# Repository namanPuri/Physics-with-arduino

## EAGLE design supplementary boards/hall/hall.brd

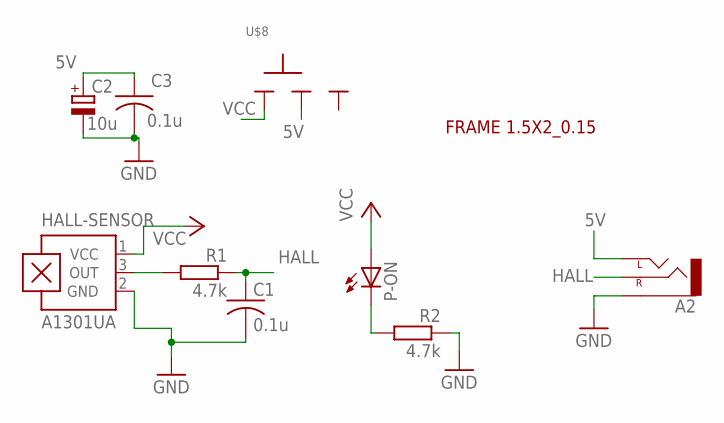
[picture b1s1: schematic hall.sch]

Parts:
A2: AUX-CONNECTOR_CEDT_JANUARY_2015_V5_AUDIO-JACKPTH; AUX-CONNECTOR_CEDT_JANUARY_2015_V5_AUDIO-JACK
C1, C3: 0.1u; C025-024X044
C2: 10u; E2,5-5
HALL-SENSOR: A1301UA; SIP3-UA
P-ON: LED3MM
R1, R2: 4.7k; 0204/7
U$1: FRAME_1.5X2_RAD_0.15
U$8: SLIDESWITCH-BIG; BIGSWITCH

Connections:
5V: A2.TIP (LEFT), C2.+, C3.1, U$8.2
GND: A2.SLEEVE, C1.2, C2.-, C3.2, HALL-SENSOR.2 (GND), R2.1
HALL: A2.RING (RIGHT), C1.1, R1.1
unnamed: HALL-SENSOR.3 (OUT), R1.2
unnamed: P-ON.K (C), R2.2
VCC: HALL-SENSOR.1 (VCC), P-ON.A, U$8.1

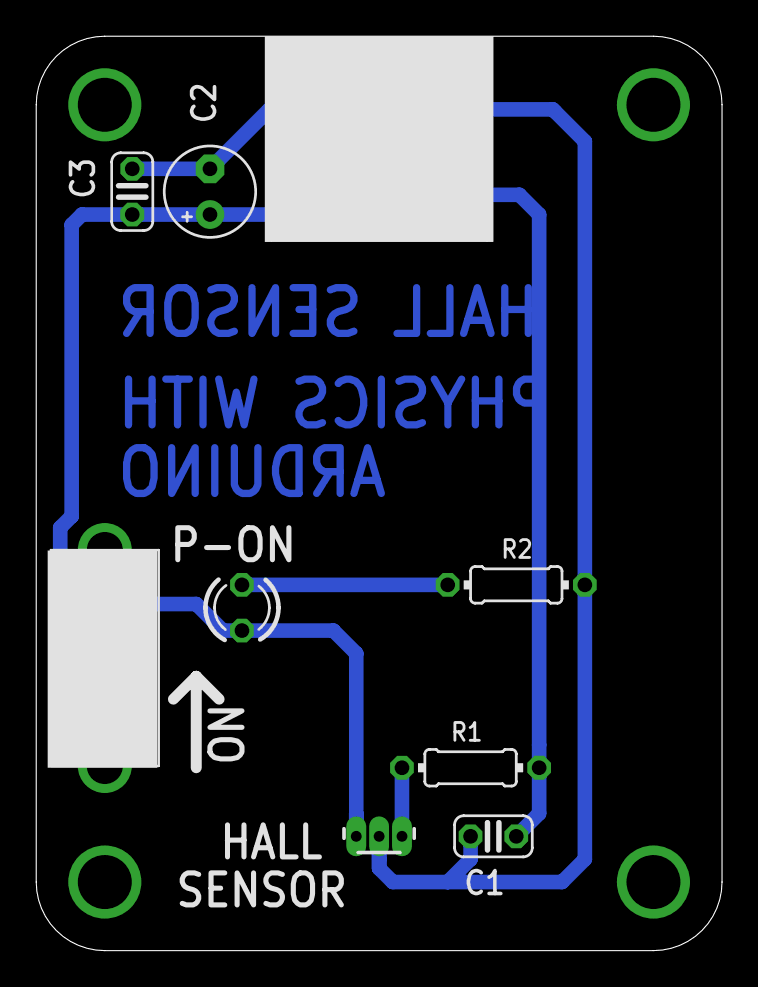
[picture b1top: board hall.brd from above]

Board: 2 copper layers, 38.1 x 50.8 mm, 10 parts (0 on the bottom side), 6 nets.

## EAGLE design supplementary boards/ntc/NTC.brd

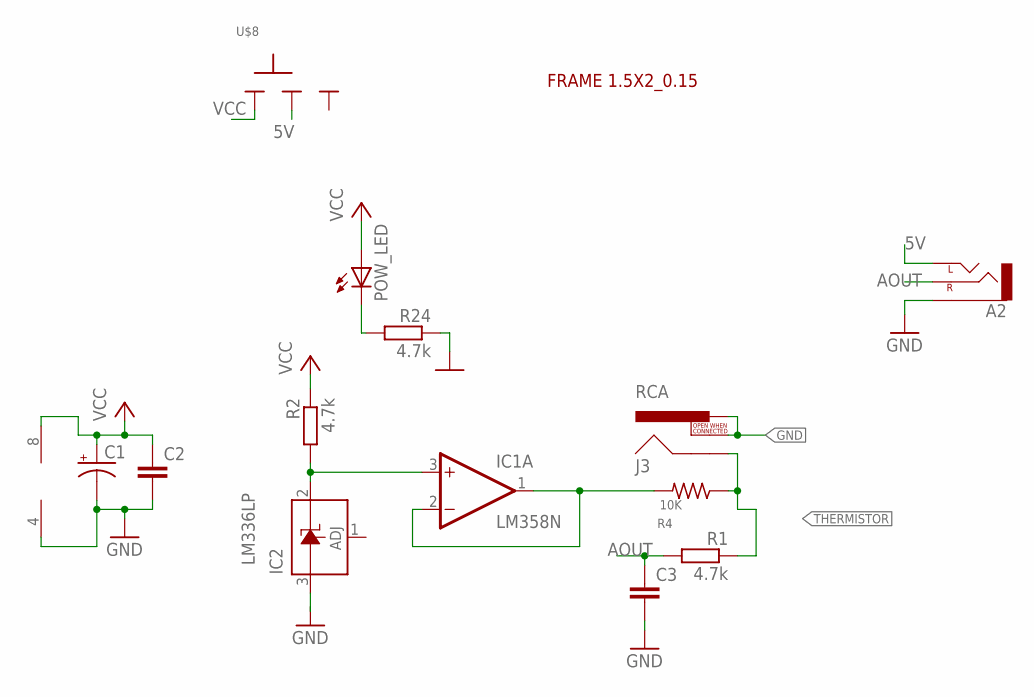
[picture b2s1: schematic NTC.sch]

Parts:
A2: AUX-CONNECTOR_CEDT_JANUARY_2015_V5_AUDIO-JACKPTH; AUX-CONNECTOR_CEDT_JANUARY_2015_V5_AUDIO-JACK
C1: CAP_POL; E2,5-5-10U
C2, C3: C-EU025-024X044; C025-024X044
IC1: LM358N; DIL08
IC2: LM336LP; TO92
J3: RCA
POW_LED: LED3MM
R1, R2, R24: 4.7k; 0204/7
R4: 10K; 0204/7
U$1: FRAME_1.5X2_RAD_0.15
U$8: SLIDESWITCH-BIG; BIGSWITCH

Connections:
5V: A2.TIP (LEFT), U$8.2
AOUT: A2.RING (RIGHT), C3.1, R1.2
GND: A2.SLEEVE, C1.-, C2.2, C3.2, IC1.4 (V-), IC2.3 (A), J3.PIN, J3.SWITCH, R24.1
unnamed: IC1.3 (+IN), IC2.2 (C), R2.2
unnamed: IC1.1 (OUT), IC1.2 (-IN), R4.2
unnamed: POW_LED.K (C), R24.2
THERMISTOR: J3.SHELL, R1.1, R4.1
VCC: C1.+, C2.1, IC1.8 (V+), POW_LED.A, R2.1, U$8.1

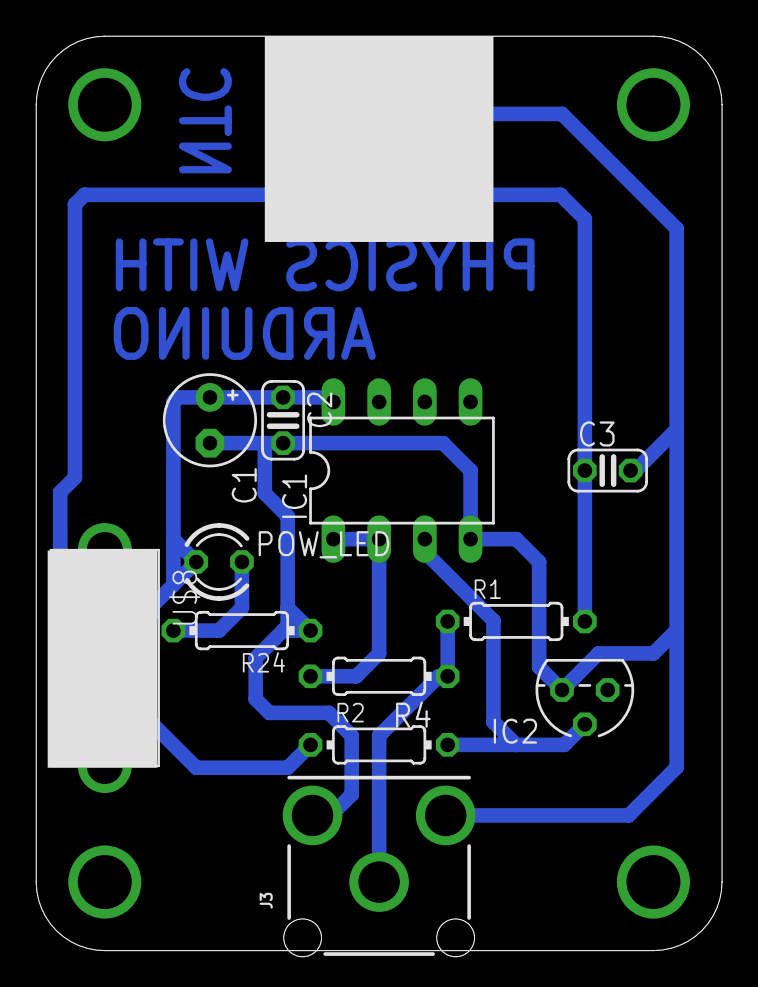
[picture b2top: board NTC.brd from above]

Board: 2 copper layers, 38.1 x 50.8 mm, 14 parts (0 on the bottom side), 8 nets.

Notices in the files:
parts and their libraries:
SparkFun-Connectors: Licensing: Creative Commons ShareAlike 4.0 International - https://creativecommons.org/licenses/by-sa/4.0
